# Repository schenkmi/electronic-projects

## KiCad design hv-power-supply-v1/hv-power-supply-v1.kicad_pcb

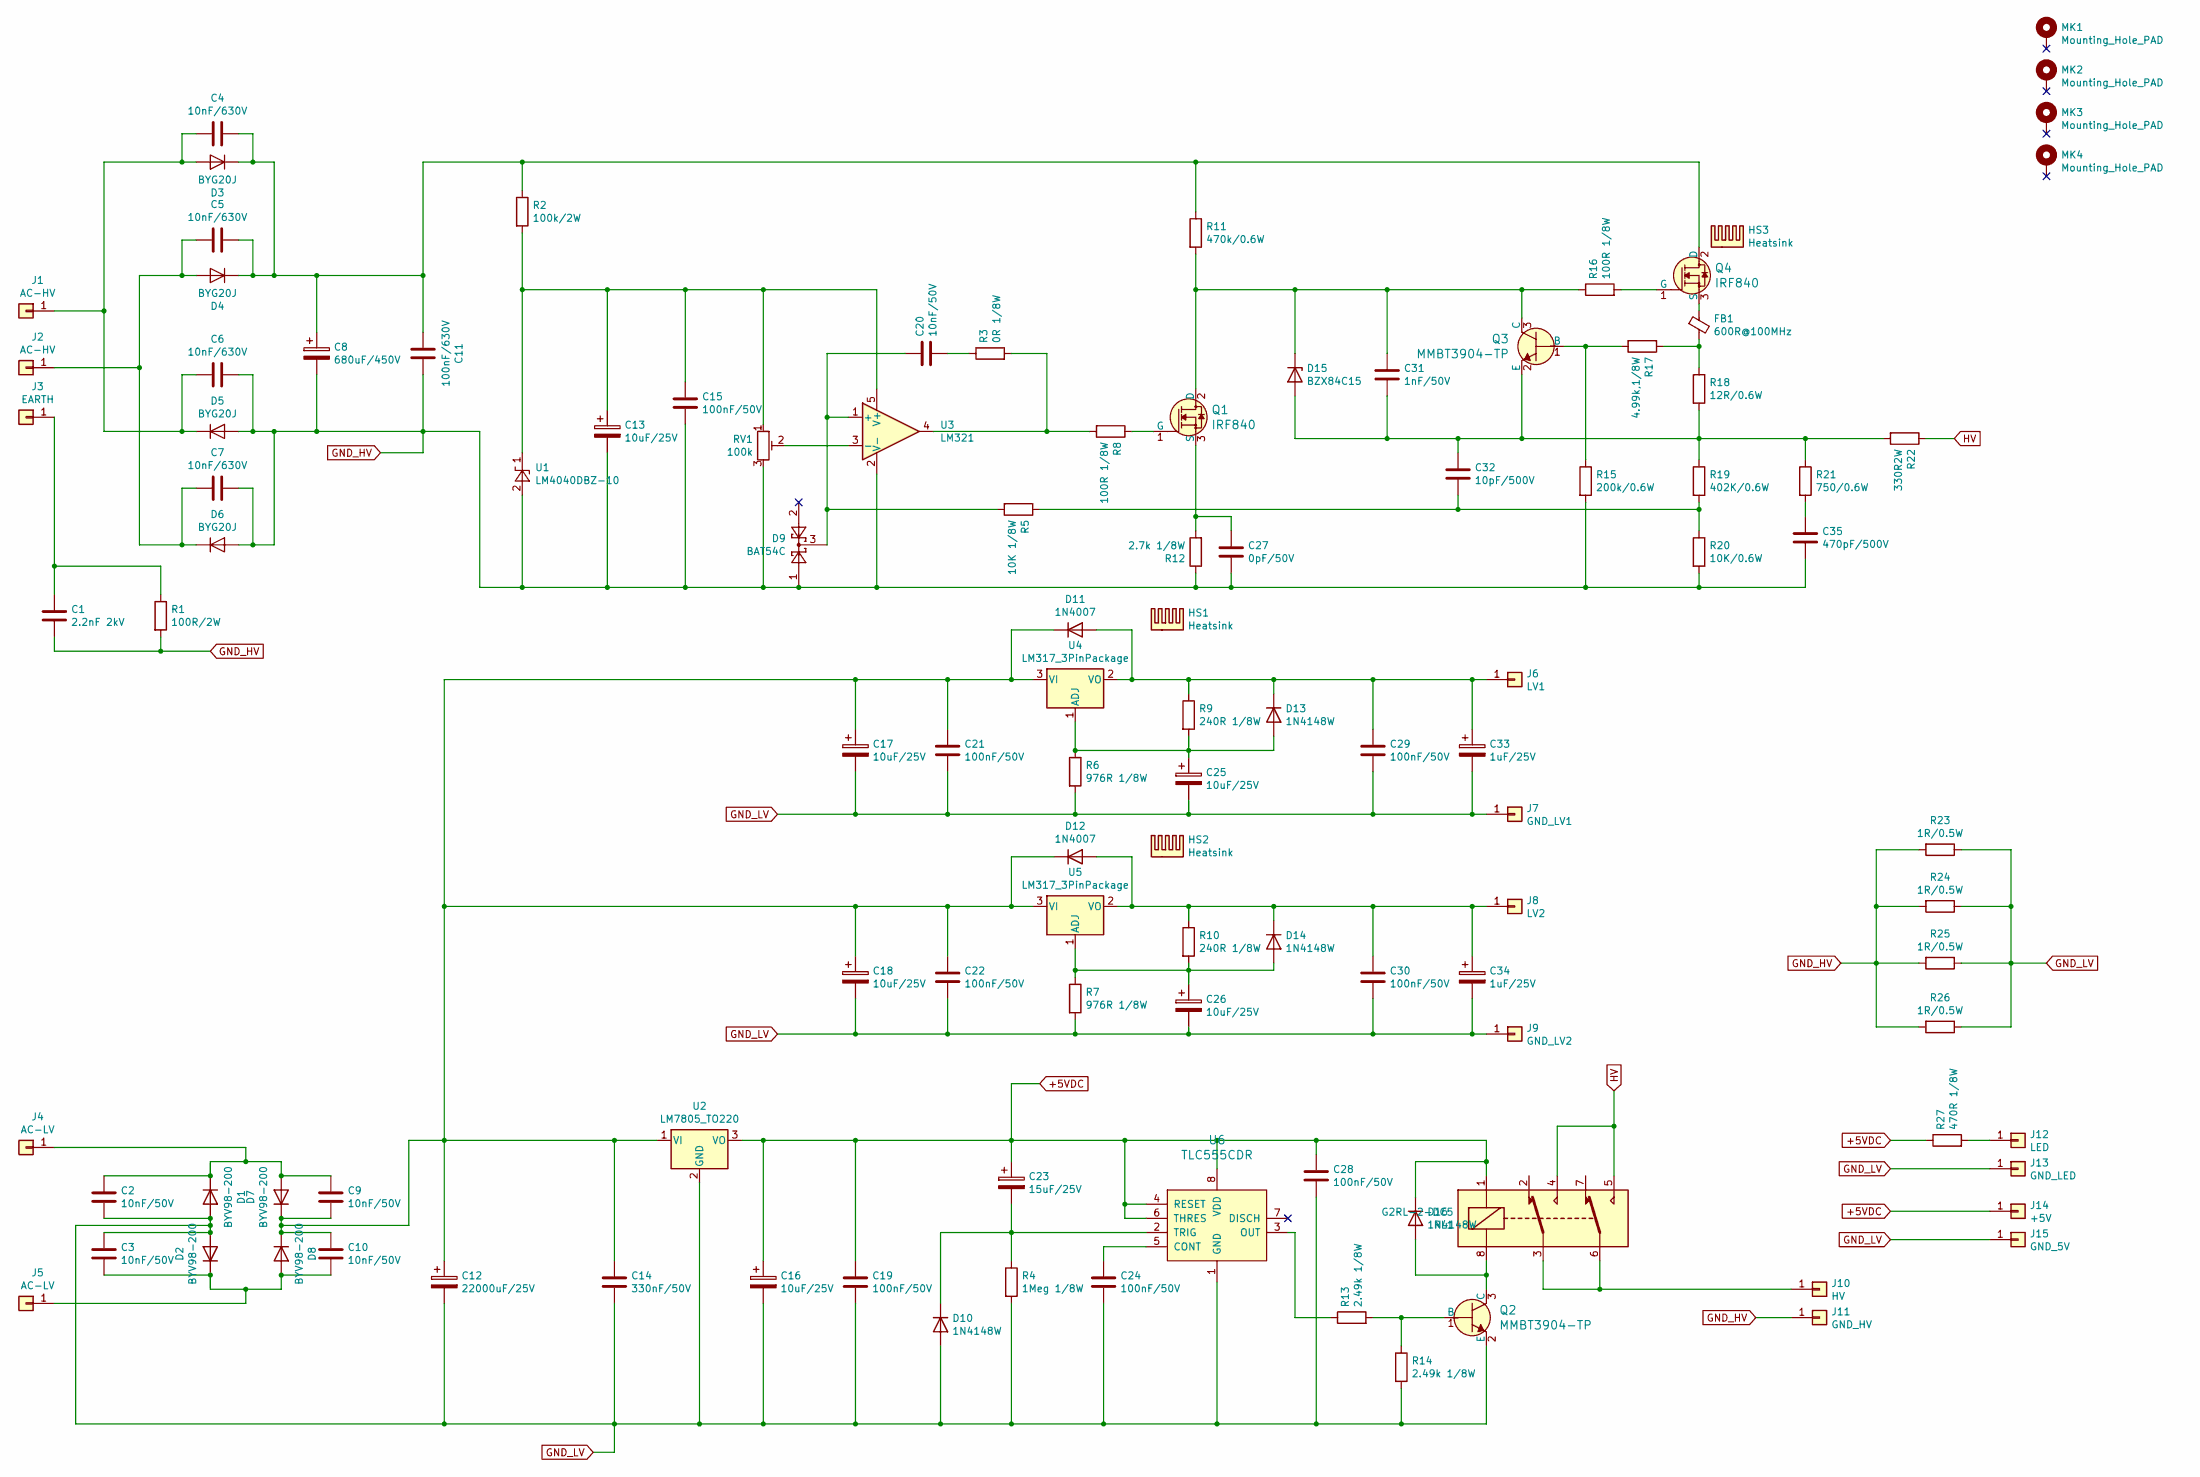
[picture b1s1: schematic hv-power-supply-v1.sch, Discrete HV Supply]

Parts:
C1: 2.2nF 2kV; C_Rect_L18.0mm_W5.0mm_P15.00mm_FKS3_FKP3
C2, C3, C9, C10, C20: 10nF/50V; C_0805_2012Metric_Pad1.18x1.45mm_HandSolder
C4, C5, C6, C7: 10nF/630V; C_Rect_L13.0mm_W4.0mm_P10.00mm_FKS3_FKP3_MKS4
C8: 680uF/450V; CP_Radial_D35.0mm_P10.00mm_SnapIn
C11: 100nF/630V; C_Rect_L18.0mm_W5.0mm_P15.00mm_FKS3_FKP3
C12: 22000uF/25V; CP_Radial_D30.0mm_P10.00mm_SnapIn
C13, C16, C17, C18, C25, C26: 10uF/25V; CP_Radial_D5.0mm_P2.00mm
C14: 330nF/50V; C_0805_2012Metric_Pad1.18x1.45mm_HandSolder
C15, C19, C21, C22, C24, C28, C29, C30: 100nF/50V; C_0805_2012Metric_Pad1.18x1.45mm_HandSolder
C23: 15uF/25V; CP_EIA-7343-31_Kemet-D_Pad2.25x2.55mm_HandSolder
C27: 0pF/50V; C_0805_2012Metric_Pad1.18x1.45mm_HandSolder
C31: 1nF/50V; C_0805_2012Metric_Pad1.18x1.45mm_HandSolder
C32: 10pF/500V; C_1206_3216Metric_Pad1.33x1.80mm_HandSolder
C33, C34: 1uF/25V; CP_Radial_D5.0mm_P2.00mm
C35: 470pF/500V; C_0805_2012Metric_Pad1.18x1.45mm_HandSolder
D1, D2, D7, D8: BYV98-200; SOD64-10
D3, D4, D5, D6: BYG20J; D_SMA_Handsoldering
D9: BAT54C; SOT-23
D10, D13, D14, D16: 1N4148W; D_SOD-123
D11, D12: 1N4007; D_DO-41_SOD81_P10.16mm_Horizontal
D15: BZX84C15; D_SOT-23_ANK
FB1: 600R@100MHz; R_0805_2012Metric_Pad1.20x1.40mm_HandSolder
HS1, HS2, HS3: Heatsink; Heatsink_Fischer_SK104-STC-STIC_35x13mm_2xDrill2.5mm
J1, J2: AC-HV; Pin_D1.3mm_L11.0mm
J3: EARTH; Pin_D1.3mm_L11.0mm
J4, J5: AC-LV; Pin_D1.3mm_L11.0mm
J6: LV1; Pin_D1.3mm_L11.0mm
J7: GND_LV1; Pin_D1.3mm_L11.0mm
J8: LV2; Pin_D1.3mm_L11.0mm
J9: GND_LV2; Pin_D1.3mm_L11.0mm
J10: HV; Pin_D1.3mm_L11.0mm
J11: GND_HV; Pin_D1.3mm_L11.0mm
J12: LED; Pin_D1.0mm_L10.0mm
J13: GND_LED; Pin_D1.0mm_L10.0mm
J14: +5V; Pin_D1.0mm_L10.0mm
J15: GND_5V; Pin_D1.0mm_L10.0mm
MK1, MK2, MK3, MK4: Mounting_Hole_PAD; MountingHole_3.2mm_M3
Q1, Q4: IRF840; TO-220-3_Vertical; MPN IRF510PBF; Digi-Key_PN IRF510PBF-ND
Q2: MMBT3904-TP; SOT-23; MPN MMBT3904-TP; Digi-Key_PN MMBT3904TPMSCT-ND
Q3: MMBT3904-TP; SOT-23_Handsoldering; MPN MMBT3904-TP; Digi-Key_PN MMBT3904TPMSCT-ND
R1: 100R/2W; R_Axial_DIN0414_L11.9mm_D4.5mm_P15.24mm_Horizontal
R2: 100k/2W; R_Axial_DIN0414_L11.9mm_D4.5mm_P15.24mm_Horizontal
R3: 0R 1/8W; R_0805_2012Metric_Pad1.20x1.40mm_HandSolder
R4: 1Meg 1/8W; R_0805_2012Metric_Pad1.20x1.40mm_HandSolder
R5: 10K 1/8W; R_0805_2012Metric_Pad1.20x1.40mm_HandSolder
R6, R7: 976R 1/8W; R_0805_2012Metric_Pad1.20x1.40mm_HandSolder
R8, R16: 100R 1/8W; R_0805_2012Metric_Pad1.20x1.40mm_HandSolder
R9, R10: 240R 1/8W; R_0805_2012Metric_Pad1.20x1.40mm_HandSolder
R11: 470k/0.6W; R_Axial_DIN0207_L6.3mm_D2.5mm_P10.16mm_Horizontal
R12: 2.7k 1/8W; R_0805_2012Metric_Pad1.20x1.40mm_HandSolder
R13, R14: 2.49k 1/8W; R_0805_2012Metric_Pad1.20x1.40mm_HandSolder
R15: 200k/0.6W; R_Axial_DIN0207_L6.3mm_D2.5mm_P10.16mm_Horizontal
R17: 4.99k,1/8W; R_0805_2012Metric_Pad1.20x1.40mm_HandSolder
R18: 12R/0.6W; R_Axial_DIN0207_L6.3mm_D2.5mm_P10.16mm_Horizontal
R19: 402K/0.6W; R_Axial_DIN0207_L6.3mm_D2.5mm_P10.16mm_Horizontal
R20: 10K/0.6W; R_Axial_DIN0207_L6.3mm_D2.5mm_P10.16mm_Horizontal
R21: 750/0.6W; R_Axial_DIN0207_L6.3mm_D2.5mm_P10.16mm_Horizontal
R22: 330R2W; R_Axial_DIN0207_L6.3mm_D2.5mm_P10.16mm_Horizontal
R23, R24, R25, R26: 1R/0.5W; R_0805_2012Metric_Pad1.20x1.40mm_HandSolder
R27: 470R 1/8W; R_0805_2012Metric_Pad1.20x1.40mm_HandSolder
RL1: G2RL-2-DC5; Relay_DPDT_Omron_G2RL
RV1: 100k; Potentiometer_Bourns_3296W_Vertical
U1: LM4040DBZ-10; SOT-23
U2: LM7805_TO220; TO-220-3_Vertical
U3: LM321; SOT-23-5_HandSoldering
U4, U5: LM317_3PinPackage; TO-220-3_Vertical
U6: TLC555CDR; SOIC-8_3.9x4.9mm_P1.27mm; MPN TLC555CDR; Digi-Key_PN 296-1336-1-ND

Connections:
+5VDC: C16.1, C19.1, C23.1, C28.1, D16.1 (K), J14.1, R27.1, RL1.1, U2.3 (VO), U6.4 (RESET), U6.6 (THRES), U6.8 (VDD)
GND_HV: C1.2, C6.1, C7.1, C8.2, C11.1, C13.2, C15.2, C27.2, C35.2, D5.2 (A), D6.2 (A), D9.1, J11.1, R1.2, R12.1, R15.2, R20.2, R23.2, R24.2, R25.2, R26.2, RV1.3, U1.2 (A), U3.2 (V-)
GND_LV: C2.2, C3.1, C12.2, C14.2, C16.2, C17.2, C18.2, C19.2, C21.2, C22.2, C24.2, C25.2, C26.2, C28.2, C29.2, C30.2, C33.2, C34.2, D1.2 (A), D2.2 (A), D10.2 (A), J7.1, J9.1, J13.1, J15.1, Q2.2 (E), R4.2, R6.2, R7.2, R14.2, R23.1, R24.1, R25.1, R26.1, U2.2 (GND), U6.1 (GND)
HV: R22.1, RL1.4, RL1.5
unnamed: C1.1, J3.1, R1.1
unnamed: C2.1, C9.1, D1.1 (K), D7.2 (A), J4.1
unnamed: C4.2, C6.2, D3.2 (A), D5.1 (K), J1.1
unnamed: C5.2, C7.2, D4.2 (A), D6.1 (K), J2.1
unnamed: C9.2, C10.1, C12.1, C14.1, C17.1, C18.1, C21.1, C22.1, D7.1 (K), D8.1 (K), D11.1 (K), D12.1 (K), U2.1 (VI), U4.3 (VI), U5.3 (VI)
unnamed: C3.2, C10.2, D2.1 (K), D8.2 (A), J5.1
unnamed: C4.1, C5.1, C8.1, C11.2, D3.1 (K), D4.1 (K), Q4.2 (D), R2.1, R11.1
unnamed: C13.1, C15.1, R2.2, RV1.1, U1.1 (K), U3.5 (V+)
unnamed: C20.1, D9.3, R5.2, U3.1 (+)
unnamed: C20.2, R3.1
unnamed: C23.2, D10.1 (K), R4.1, U6.2 (TRIG)
unnamed: C24.1, U6.5 (CONT)
unnamed: C25.1, D13.2 (A), R6.1, R9.2, U4.1 (ADJ)
unnamed: C26.1, D14.2 (A), R7.1, R10.2, U5.1 (ADJ)
unnamed: C27.1, Q1.3 (S), R12.2
unnamed: C29.1, C33.1, D11.2 (A), D13.1 (K), J6.1, R9.1, U4.2 (VO)
unnamed: C30.1, C34.1, D12.2 (A), D14.1 (K), J8.1, R10.1, U5.2 (VO)
unnamed: C31.1, D15.1 (K), Q1.2 (D), Q3.3 (C), R11.2, R16.1
unnamed: C31.2, C32.1, D15.2 (A), Q3.2 (E), R18.2, R19.1, R21.1, R22.2
unnamed: C32.2, R5.1, R19.2, R20.1
unnamed: C35.1, R21.2
unnamed: D16.2 (A), Q2.3 (C), RL1.8
unnamed: FB1.1, Q4.3 (S)
unnamed: FB1.2, R17.1, R18.1
unnamed: J10.1, RL1.3, RL1.6
unnamed: J12.1, R27.2
unnamed: Q1.1 (G), R8.1
unnamed: Q2.1 (B), R13.2, R14.1
unnamed: Q3.1 (B), R15.1, R17.2
unnamed: Q4.1 (G), R16.2
unnamed: R3.2, R8.2, U3.4
unnamed: R13.1, U6.3 (OUT)
unnamed: RV1.2, U3.3 (-)

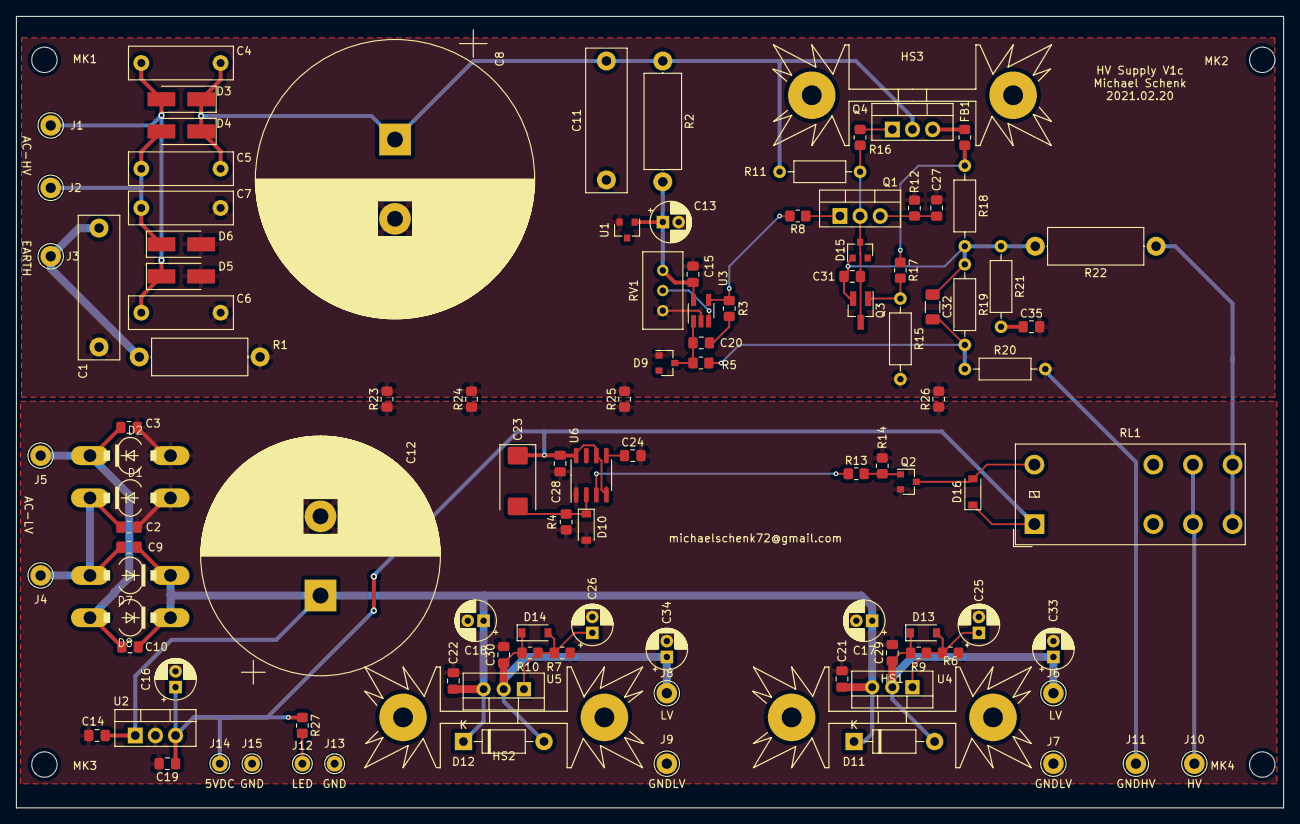
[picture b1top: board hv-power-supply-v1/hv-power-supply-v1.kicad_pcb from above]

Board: 2 copper layers, 159.9 x 99.9 mm, 113 parts (0 on the bottom side), 37 nets.

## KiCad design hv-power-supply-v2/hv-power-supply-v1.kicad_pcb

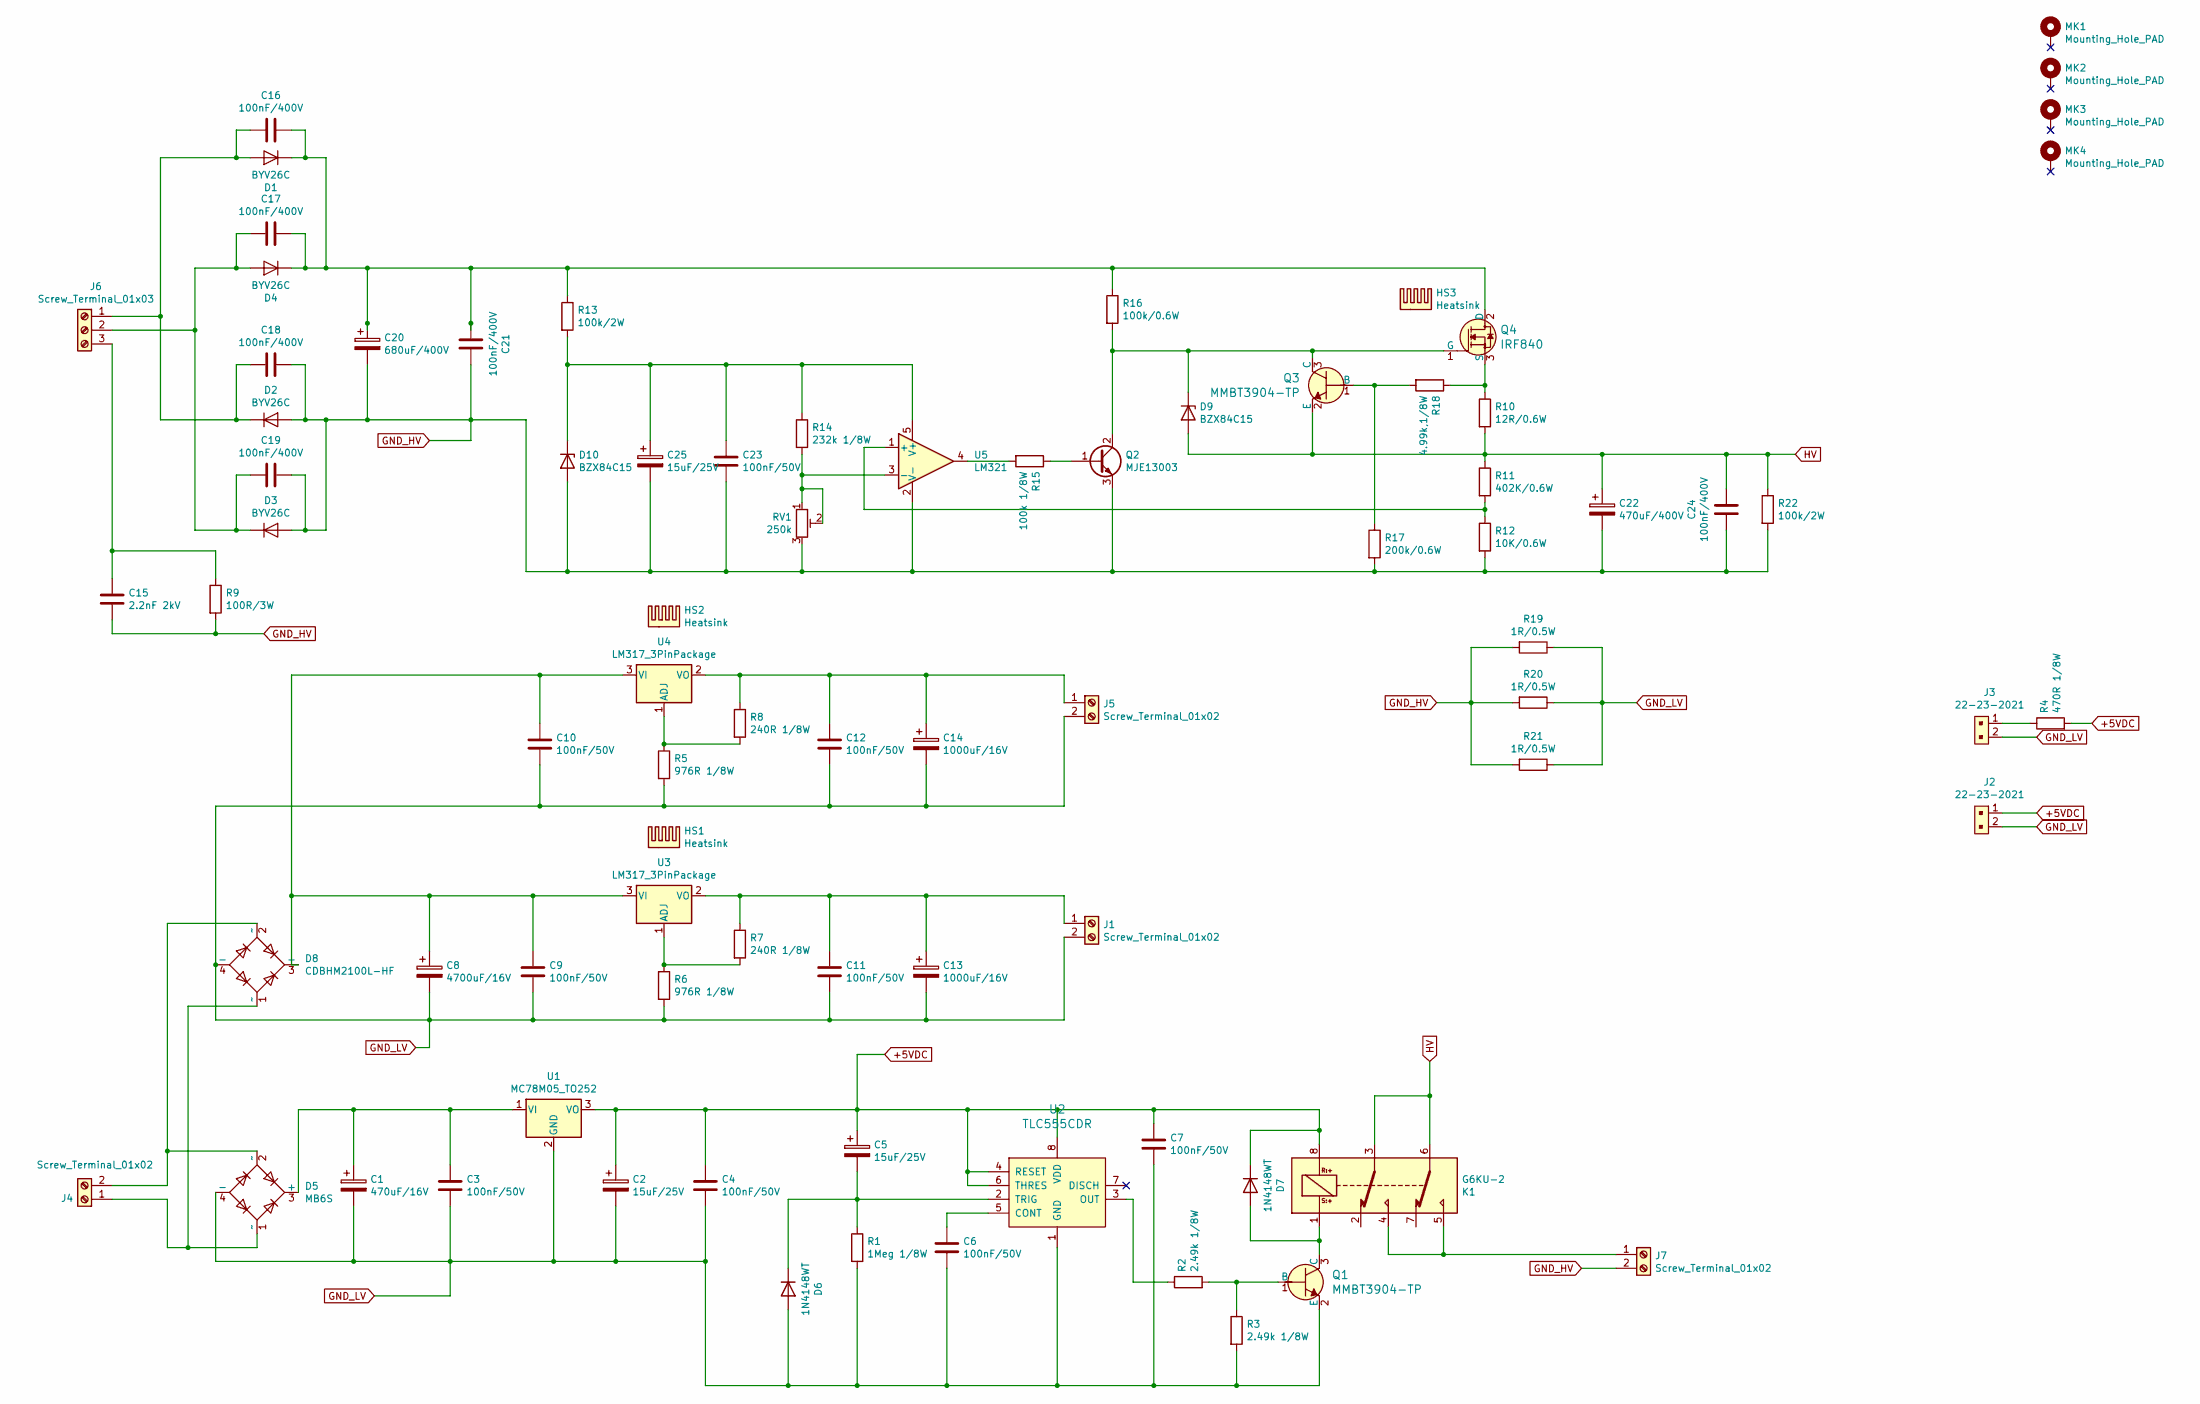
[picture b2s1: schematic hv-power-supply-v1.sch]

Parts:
C1: 470uF/16V; CP_Radial_D8.0mm_P3.50mm
C2, C5, C25: 15uF/25V; CP_Tantalum_Case-T_EIA-3528-12_Hand
C3, C4, C6, C7, C9, C10, C11, C12, C23: 100nF/50V; C_1206_HandSoldering
C8: 4700uF/16V; CP_Radial_D16.0mm_P7.50mm
C13, C14: 1000uF/16V; CP_Radial_D10.0mm_P5.00mm
C15: 2.2nF 2kV; C_Rect_L18.0mm_W5.0mm_P15.00mm_FKS3_FKP3
C16, C17, C18, C19, C21, C24: 100nF/400V; C_Rect_L18.0mm_W7.0mm_P15.00mm_FKS3_FKP3
C20: 680uF/400V; CP_Radial_D35.0mm_P10.00mm_SnapIn
C22: 470uF/400V; CP_Radial_D35.0mm_P10.00mm_SnapIn
D1, D2, D3, D4: BYV26C; D_DO-41_SOD81_P10.16mm_Horizontal
D5: MB6S; Diode_Bridge_TO-269AA
D6, D7: 1N4148WT; D_SOD-523
D8: CDBHM2100L-HF; Diode_Bridge_TO-269AA
D9, D10: BZX84C15; D_SOT-23_ANK
HS1, HS2, HS3: Heatsink; Heatsink_Fischer_SK104-STC-STIC_35x13mm_2xDrill2.5mm
J1, J4, J5, J7: Screw_Terminal_01x02; TerminalBlock_Altech_AK300-2_P5.00mm
J2, J3: 22-23-2021; PinHeader_1x2_P2.54mm_Drill1.02mm; MPN 22-23-2021; Digi-Key_PN WM4200-ND
J6: Screw_Terminal_01x03; TerminalBlock_Altech_AK300-3_P5.00mm
K1: G6KU-2; Relay_DPDT_Omron_G2RL-2
MK1, MK2, MK3, MK4: Mounting_Hole_PAD; MountingHole_3.2mm_M3
Q1, Q3: MMBT3904-TP; SOT-23; MPN MMBT3904-TP; Digi-Key_PN MMBT3904TPMSCT-ND
Q2: MJE13003; TO-126_Vertical
Q4: IRF840; TO-220-3_Vertical; MPN IRF510PBF; Digi-Key_PN IRF510PBF-ND
R1: 1Meg 1/8W; R_0805_HandSoldering
R2, R3: 2.49k 1/8W; R_0805_HandSoldering
R4: 470R 1/8W; R_0805_HandSoldering
R5, R6: 976R 1/8W; R_0805_HandSoldering
R7, R8: 240R 1/8W; R_0805_HandSoldering
R9: 100R/3W; R_Axial_DIN0516_L15.5mm_D5.0mm_P25.40mm_Horizontal
R10: 12R/0.6W; R_Axial_DIN0207_L6.3mm_D2.5mm_P10.16mm_Horizontal
R11: 402K/0.6W; R_Axial_DIN0207_L6.3mm_D2.5mm_P10.16mm_Horizontal
R12: 10K/0.6W; R_Axial_DIN0207_L6.3mm_D2.5mm_P10.16mm_Horizontal
R13, R22: 100k/2W; R_Axial_DIN0309_L9.0mm_D3.2mm_P12.70mm_Horizontal
R14: 232k 1/8W; R_0805_HandSoldering
R15: 100k 1/8W; R_0805_HandSoldering
R16: 100k/0.6W; R_Axial_DIN0207_L6.3mm_D2.5mm_P10.16mm_Horizontal
R17: 200k/0.6W; R_Axial_DIN0207_L6.3mm_D2.5mm_P10.16mm_Horizontal
R18: 4.99k,1/8W; R_0805_HandSoldering
R19, R20, R21: 1R/0.5W; R_1210_HandSoldering
RV1: 250k; Potentiometer_Trimmer_Bourns_3299W
U1: MC78M05_TO252; TO-252-2
U2: TLC555CDR; SOIC-8_W3.9mm; MPN TLC555CDR; Digi-Key_PN 296-1336-1-ND
U3, U4: LM317_3PinPackage; TO-220-3_Vertical
U5: LM321; SOT-23-5_HandSoldering

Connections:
+5VDC: C2.1, C4.1, C5.1, C7.1, D7.1 (K), J2.1, K1.8, R4.2, U1.3 (VO), U2.4 (RESET), U2.6 (THRES), U2.8 (VDD)
GND_HV: C15.2, C18.1, C19.1, C20.2, C21.1, C22.2, C23.2, C24.2, C25.2, D2.2 (A), D3.2 (A), D10.2 (A), J7.2, Q2.3 (E), R9.2, R12.2, R17.2, R19.2, R20.2, R21.2, R22.2, RV1.3, U5.2 (V-)
GND_LV: C1.2, C2.2, C3.2, C4.2, C6.2, C7.2, C8.2, C9.2, C10.2, C11.2, C12.2, C13.2, C14.2, D5.4 (-), D6.2 (A), D8.4 (-), J1.2, J2.2, J3.2, J5.2, Q1.2 (E), R1.2, R3.2, R5.2, R6.2, R19.1, R20.1, R21.1, U1.2 (GND), U2.1 (GND)
HV: C22.1, C24.1, D9.2 (A), K1.3, K1.6, Q3.2 (E), R10.2, R11.1, R22.1
unnamed: C1.1, C3.1, D5.3 (+), U1.1 (VI)
unnamed: C5.2, D6.1 (K), R1.1, U2.2 (TRIG)
unnamed: C6.1, U2.5 (CONT)
unnamed: C8.1, C9.1, C10.1, D8.3 (+), U3.3 (VI), U4.3 (VI)
unnamed: C11.1, C13.1, J1.1, R7.1, U3.2 (VO)
unnamed: C12.1, C14.1, J5.1, R8.1, U4.2 (VO)
unnamed: C15.1, J6.3, R9.1
unnamed: C16.1, C17.1, C20.1, C21.2, D1.1 (K), D4.1 (K), Q4.2 (D), R13.1, R16.1
unnamed: C16.2, C18.2, D1.2 (A), D2.1 (K), J6.1
unnamed: C17.2, C19.2, D3.1 (K), D4.2 (A), J6.2
unnamed: C23.1, C25.1, D10.1 (K), R13.2, R14.1, U5.5 (V+)
unnamed: D5.1 (~~), D8.1 (~~), J4.1
unnamed: D5.2 (~~), D8.2 (~~), J4.2
unnamed: D7.2 (A), K1.1, Q1.3 (C)
unnamed: D9.1 (K), Q2.2 (C), Q3.3 (C), Q4.1 (G), R16.2
unnamed: J3.1, R4.1
unnamed: J7.1, K1.4, K1.5
unnamed: Q1.1 (B), R2.2, R3.1
unnamed: Q2.1 (B), R15.1
unnamed: Q3.1 (B), R17.1, R18.2
unnamed: Q4.3 (S), R10.1, R18.1
unnamed: R2.1, U2.3 (OUT)
unnamed: R5.1, R8.2, U4.1 (ADJ)
unnamed: R6.1, R7.2, U3.1 (ADJ)
unnamed: R11.2, R12.1, U5.1 (+)
unnamed: R14.2, RV1.1, RV1.2, U5.3 (-)
unnamed: R15.2, U5.4

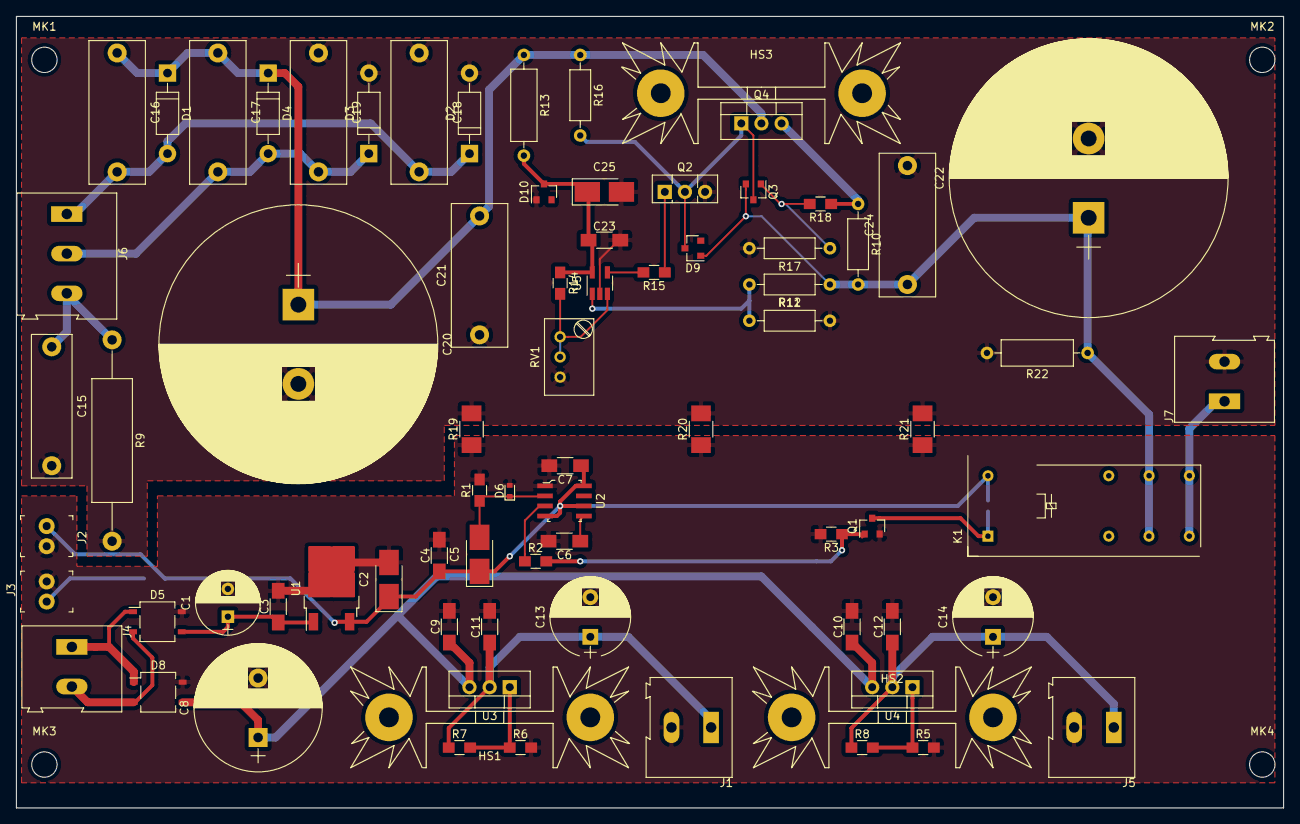
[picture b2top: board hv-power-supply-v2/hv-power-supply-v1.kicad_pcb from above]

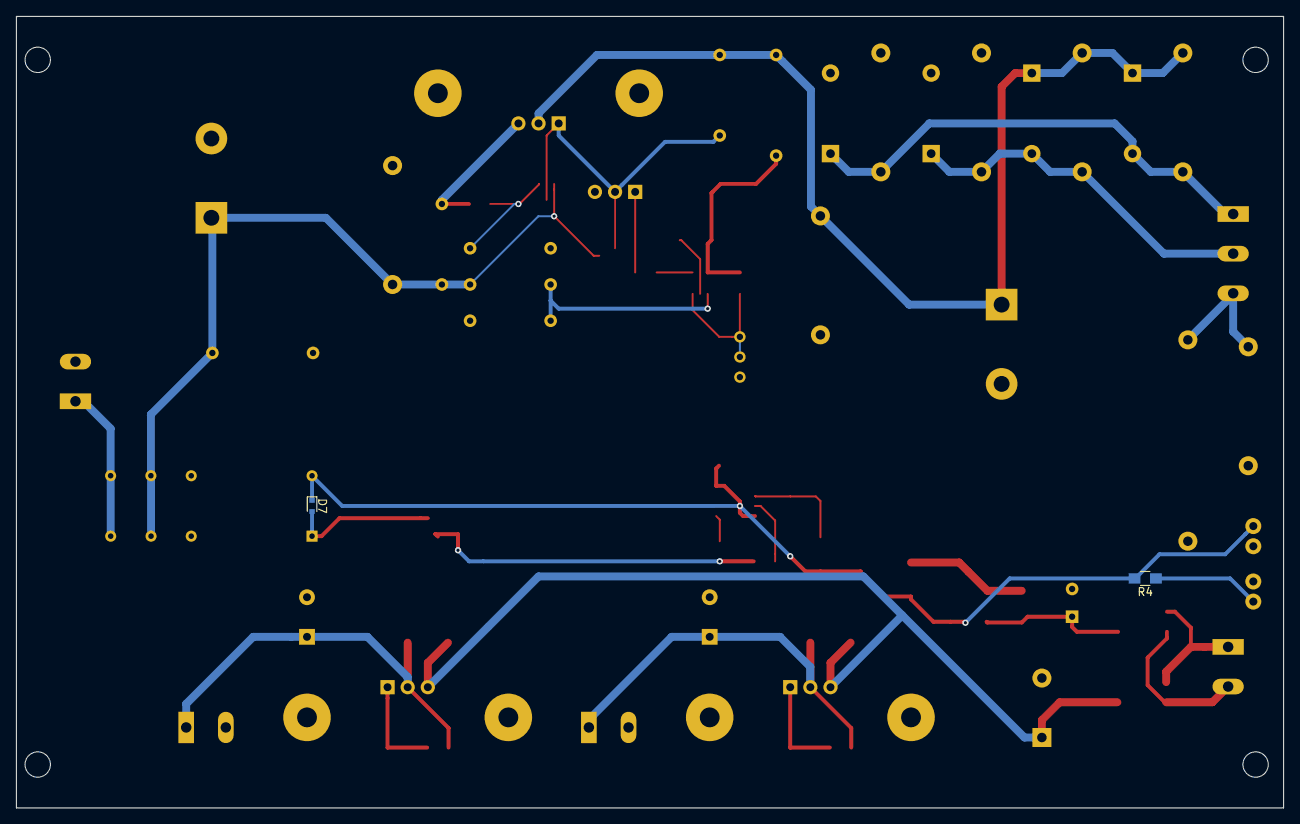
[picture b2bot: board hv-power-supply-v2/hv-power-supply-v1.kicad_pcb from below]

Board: 2 copper layers, 159.9 x 99.9 mm, 82 parts (2 on the bottom side), 31 nets.

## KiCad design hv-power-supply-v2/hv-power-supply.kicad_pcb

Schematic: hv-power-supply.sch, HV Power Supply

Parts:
C1: 2.2nF/2kV; C_Rect_L18.0mm_W5.0mm_P15.00mm_FKS3_FKP3
C2, C3, C6, C7: 10nF/630VDC; C_Rect_L13.0mm_W4.0mm_P10.00mm_FKS3_FKP3_MKS4
C4, C5, C8, C9: 10nF/50V; C_0805_2012Metric_Pad1.18x1.45mm_HandSolder
C10: 680uF/450VDC; CP_Radial_D35.0mm_P10.00mm_SnapIn
C11: 100nF/630V; C_Rect_L18.0mm_W5.0mm_P15.00mm_FKS3_FKP3
C12: 1uF/1kV; C_Rect_L32.0mm_W15.0mm_P27.00mm
C13: 2.2uF/450VDC; CP_Radial_D10.0mm_P5.00mm
C14: 22000uF/25VDC; CP_Radial_D30.0mm_P10.00mm_SnapIn
C15, C18, C21, C22: 100nF/50V; C_0805_2012Metric_Pad1.18x1.45mm_HandSolder
C16: 330nF/50V; C_0805_2012Metric_Pad1.18x1.45mm_HandSolder
C17: 10uF/25V; CP_Radial_D5.0mm_P2.00mm
C19: 1uF/25V; CP_Radial_D5.0mm_P2.00mm
C20: 15uF/25V; CP_EIA-7343-31_Kemet-D_Pad2.25x2.55mm_HandSolder
D1, D2, D5, D6: BYG20D; D_SMA_Handsoldering
D3, D4, D7, D8: BYV98-200; D_DO-41_SOD81_P10.16mm_Horizontal
D9, D10: 1N4736A/6.3V; D_DO-41_SOD81_P10.16mm_Horizontal
D11, D12: 1N4007; D_DO-41_SOD81_P10.16mm_Horizontal
D13, D14: 1N4148W; D_SOD-123
H1, H2, H3, H4: MountingHole; MountingHole_3.2mm_M3
HS1, HS2, HS3: Heatsink; Heatsink_Fischer_SK104-STC-STIC_35x13mm_2xDrill2.5mm
J1: Screw_Terminal_01x03; TerminalBlock_Altech_AK300-3_P5.00mm
J2: Screw_Terminal_01x02; TerminalBlock_Altech_AK300-2_P5.00mm
J3: HV; Pin_D1.3mm_L11.0mm
J4: GND_HV; Pin_D1.3mm_L11.0mm
J5: LV; Pin_D1.3mm_L11.0mm
J6: GND_LV; Pin_D1.3mm_L11.0mm
J7: LED; Pin_D1.0mm_L10.0mm
J8, J10: GND_LV; Pin_D1.0mm_L10.0mm
J9: +5V; Pin_D1.0mm_L10.0mm
Q1: Q_NMOS_SGD; TO-92
Q2: IRF840; TO-220-3_Vertical
Q3: MMBT3904; SOT-23
R1: 100R/3W; R_Axial_DIN0617_L17.0mm_D6.0mm_P25.40mm_Horizontal
R2: 4.7k; R_0805_2012Metric_Pad1.20x1.40mm_HandSolder
R3: 100R; R_0805_2012Metric_Pad1.20x1.40mm_HandSolder
R4: 20R/2W; R_Axial_DIN0411_L9.9mm_D3.6mm_P15.24mm_Horizontal
R5: 100k/2W; R_Axial_DIN0411_L9.9mm_D3.6mm_P15.24mm_Horizontal
R6: 1k/2W; R_Axial_DIN0411_L9.9mm_D3.6mm_P15.24mm_Horizontal
R7: 976R; R_0805_2012Metric_Pad1.20x1.40mm_HandSolder
R8: 240R; R_0805_2012Metric_Pad1.20x1.40mm_HandSolder
R9: 1Meg; R_0805_2012Metric_Pad1.20x1.40mm_HandSolder
R10, R11: 2.49k; R_0805_2012Metric_Pad1.20x1.40mm_HandSolder
R12, R13, R14: 0R; R_1206_3216Metric_Pad1.30x1.75mm_HandSolder
R15: 330R; R_0805_2012Metric_Pad1.20x1.40mm_HandSolder
RL1: G2RL-2-DC5; Relay_DPDT_Omron_G2RL
RV1: 500k; Potentiometer_Bourns_3296W_Vertical
U1: LT3080xT; TO-220-5_P3.4x3.7mm_StaggerOdd_Lead3.8mm_Vertical
U2: LM317_TO-220; TO-220-3_Vertical
U3: LM7805_TO220; TO-220-3_Vertical
U4: TLC555xD; SOIC-8_3.9x4.9mm_P1.27mm

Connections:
GND_HV: C1.1, C2.2, C3.1, C10.2, C11.2, C12.2, C13.2, D1.2 (A), D2.2 (A), J4.1, R1.1, R12.1, R13.1, R14.1, RV1.2, RV1.3
GND_LV: C4.2, C5.1, C14.2, C15.2, C16.2, C17.2, C18.2, C19.2, C21.2, C22.2, D3.2 (A), D4.2 (A), D13.2 (A), J6.1, J8.1, J10.1, Q3.2 (E), R7.2, R9.2, R11.2, R12.2, R13.2, R14.2, U4.1 (GND)
unnamed: C1.2, J1.3, R1.2
unnamed: C2.1, C6.1, D1.1 (K), D5.2 (A), J1.1
unnamed: C3.2, C7.2, D2.1 (K), D6.2 (A), J1.2
unnamed: C4.1, C8.1, D3.1 (K), D7.2 (A), J2.1
unnamed: C5.2, C9.2, D4.1 (K), D8.2 (A), J2.2
unnamed: C6.2, C7.1, C10.1, C11.1, D5.1 (K), D6.1 (K), Q1.3 (D), Q2.2 (D)
unnamed: C12.1, D9.2 (A), R4.1, U1.4 (VCONTROL), U1.5 (IN)
unnamed: C13.1, D10.2 (A), R6.2, RL1.4, RL1.5, U1.3 (OUT)
unnamed: C8.2, C9.1, C14.1, C15.1, C16.1, D7.1 (K), D8.1 (K), D11.1, U2.3, U3.1
unnamed: C17.1, D12.2, R7.1, R8.2, U2.1
unnamed: C18.1, C20.1, C22.1, D14.1 (K), J9.1, R15.2, RL1.1, U3.3, U4.4 (R), U4.6 (THR), U4.8 (VCC)
unnamed: C19.1, D11.2, D12.1, J5.1, R8.1, U2.2
unnamed: C20.2, D13.1 (K), R9.1, U4.2 (TR)
unnamed: C21.1, U4.5 (CV)
unnamed: D9.1 (K), D10.1 (K), Q1.2 (G), R2.1, R3.1
unnamed: D14.2 (A), Q3.3 (C), RL1.8
unnamed: J3.1, RL1.3, RL1.6
unnamed: J7.1, R15.1
unnamed: Q1.1 (S), R2.2
unnamed: Q2.1 (G), R3.2
unnamed: Q2.3 (S), R4.2
unnamed: Q3.1 (B), R10.1, R11.1
unnamed: R5.1, R6.1, RV1.1
unnamed: R5.2, U1.2 (SET)
unnamed: R10.2, U4.3 (Q)

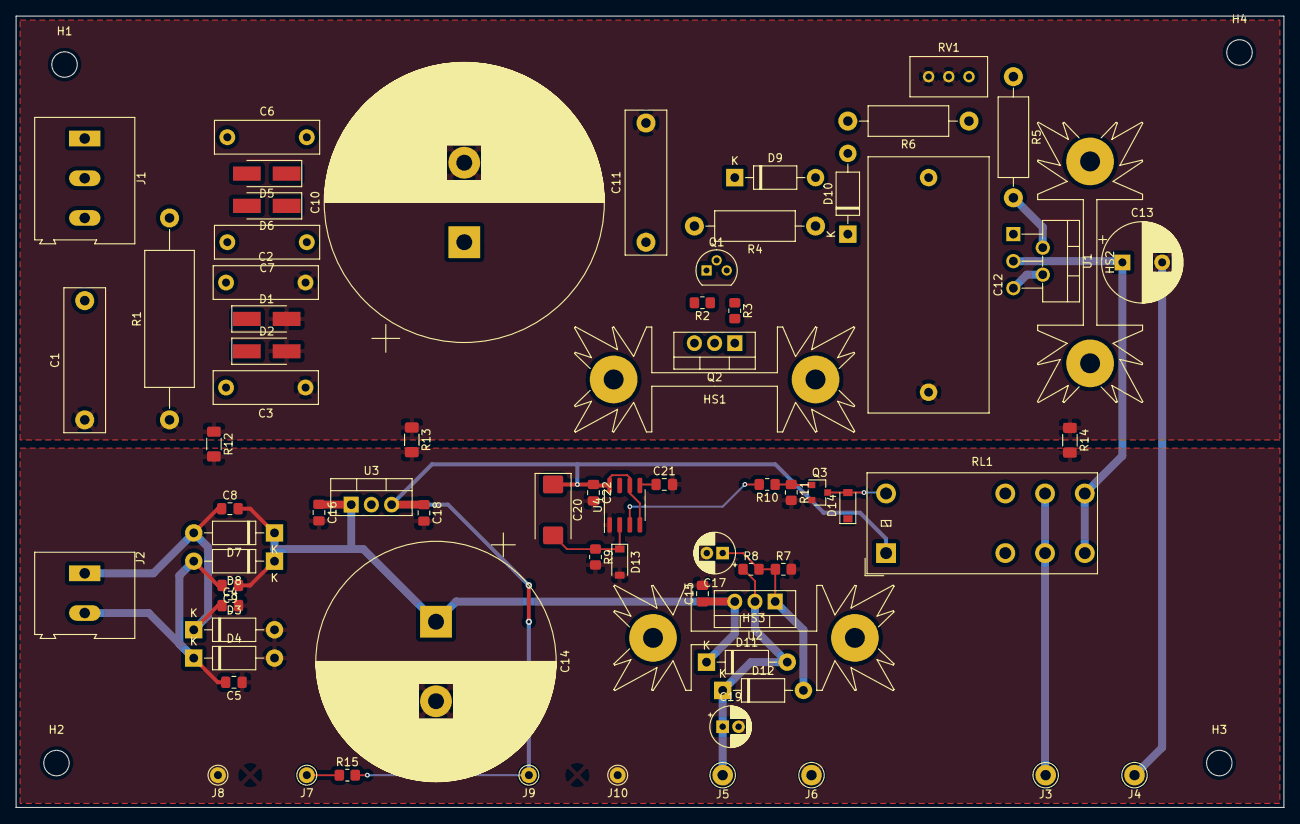
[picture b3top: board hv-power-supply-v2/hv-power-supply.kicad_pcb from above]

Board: 2 copper layers, 159.5 x 99.6 mm, 77 parts (0 on the bottom side), 27 nets.
